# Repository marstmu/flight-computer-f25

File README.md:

# MARS Flight Computer F25

---

<div align="center">
  <div>

    <p><em>3D Render</em></p>
  </div>
  <br>

  <div>
    <br>
    <p><em>Schematic</em></p>
  </div>
  <br>
  
  <div>
    
    <br>
    <em>Footprint</em>
  </div>
</div>

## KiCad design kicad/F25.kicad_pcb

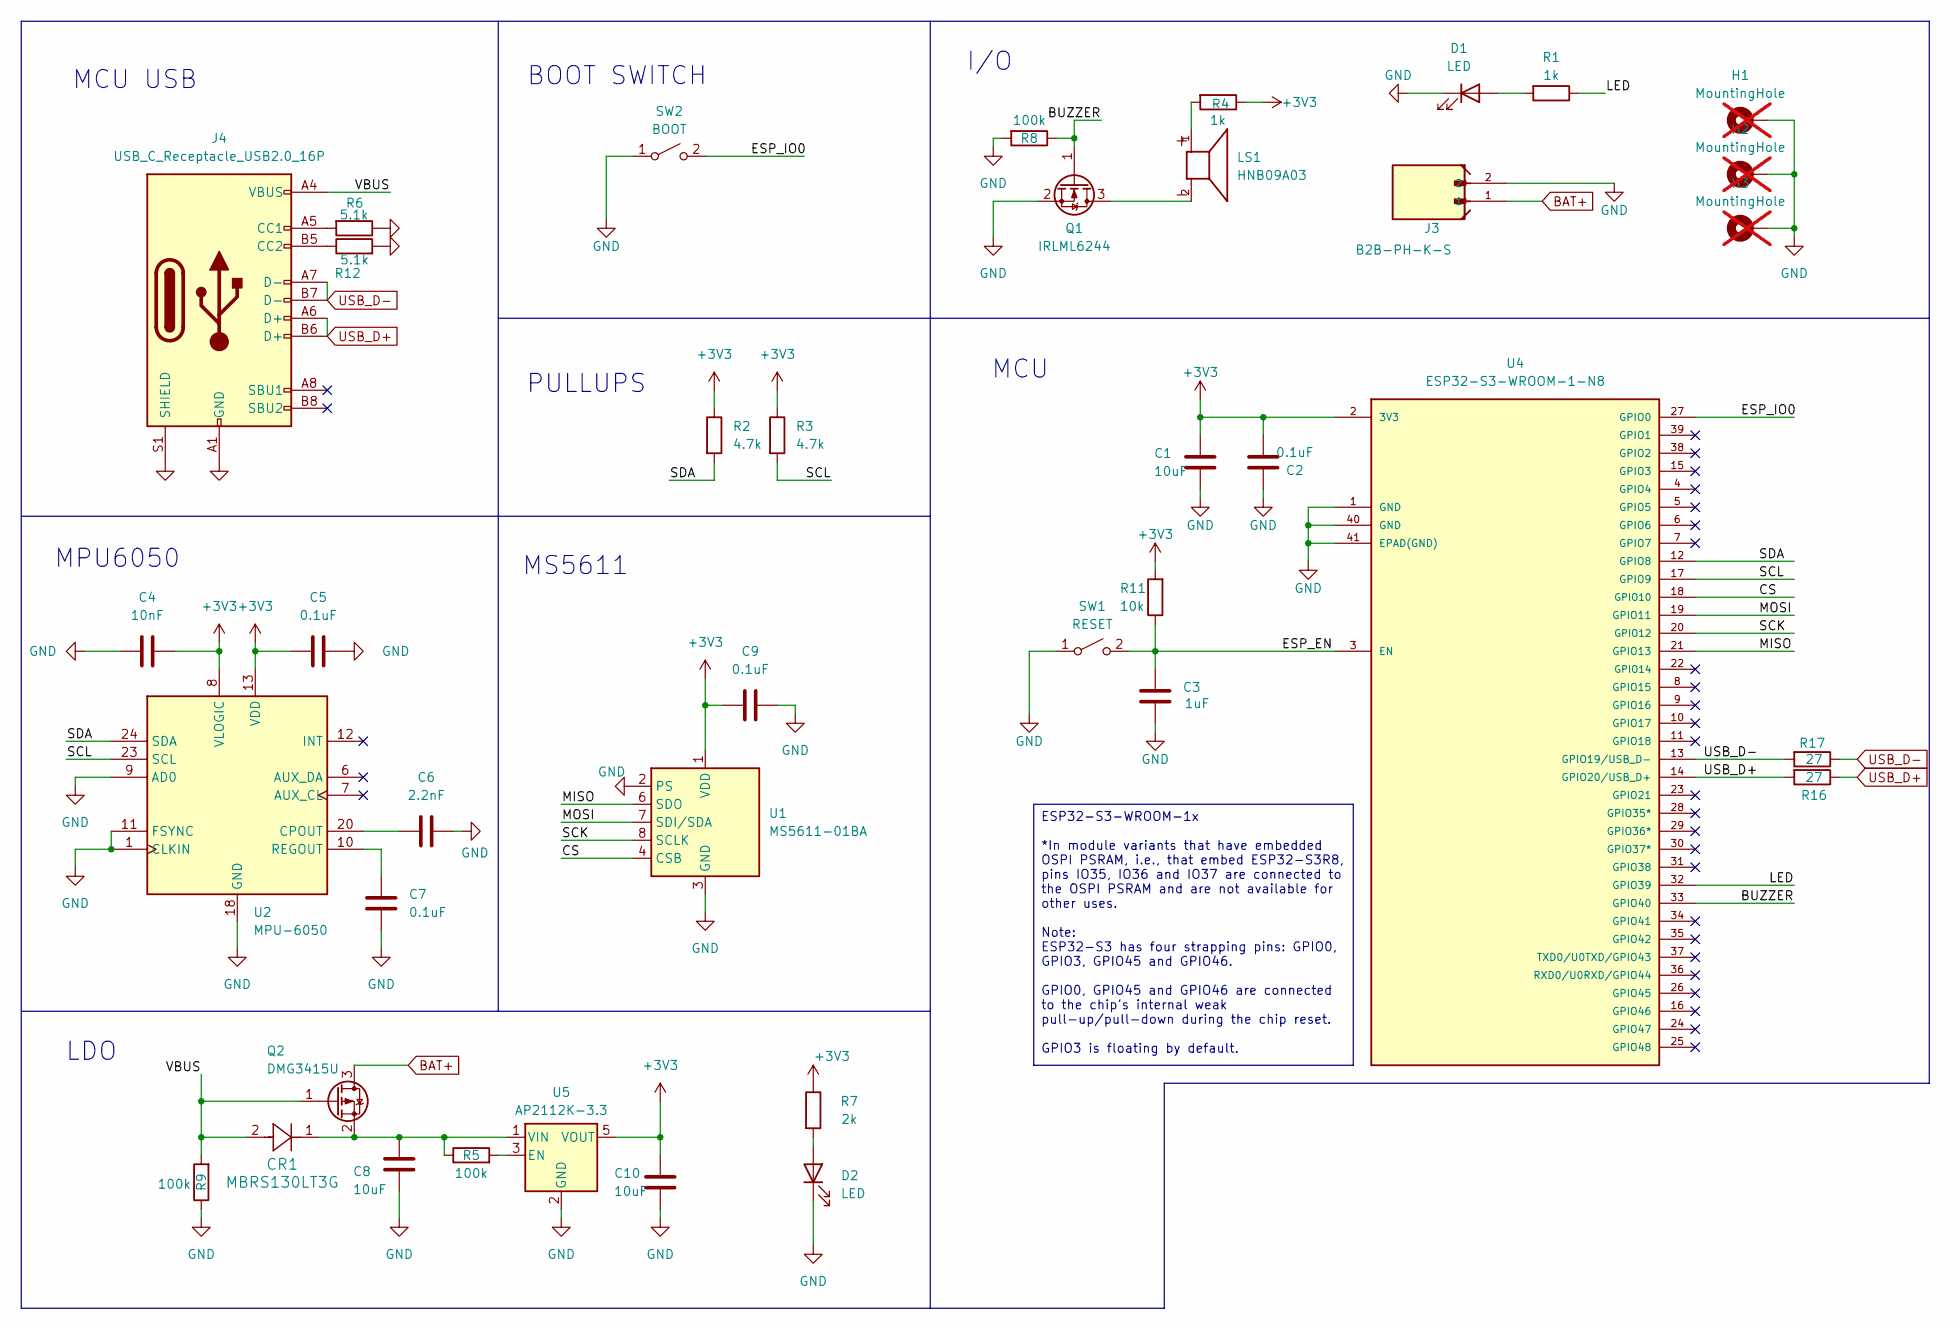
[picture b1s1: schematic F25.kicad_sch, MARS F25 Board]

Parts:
C1, C8, C10: 10uF; C_0402_1005Metric; LCSC C15525
C2, C5, C7, C9: 0.1uF; C_0402_1005Metric; LCSC C1525
C3: 1uF; C_0402_1005Metric; LCSC C52923
C4: 10nF; C_0402_1005Metric; LCSC C15195
C6: 2.2nF; C_0402_1005Metric; LCSC C84703
CR1: MBRS130LT3G; DIODE_SMB_2L_ONS; LCSC C51771
D1: LED; LED_0603_1608Metric; LCSC C2288
D2: LED; LED_0603_1608Metric; LCSC C2290
H1, H2, H3: MountingHole; hole; not fitted
J3: B2B-PH-K-S; JST_B2B-PH-K-S; LCSC C131337
J4: USB_C_Receptacle_USB2.0_16P; USB_C_Receptacle_Palconn_UTC16-G; LCSC Part # C2765186
LS1: HNB09A03; PARTREV C; LCSC C96102
Q1: IRLML6244; SOT-23; LCSC C5123965
Q2: DMG3415U; SOT-23; LCSC C7202986
R1, R4: 1k; C_0402_1005Metric; LCSC C11702
R2, R3: 4.7k; C_0402_1005Metric; LCSC C25900
R5, R8, R9: 100k; C_0402_1005Metric; LCSC C25741
R6, R12: 5.1k; R_0402_1005Metric; LCSC Part # C25905
R7: 2k; C_0402_1005Metric; LCSC C4109
R11: 10k; C_0402_1005Metric; LCSC C25744
R16, R17: 27; R_0402_1005Metric; LCSC Part # C25100
SW1: RESET; SW_SPST_B3U-1000P; LCSC C231329
SW2: BOOT; SW_SPST_B3U-1000P; LCSC C231329
U1: MS5611-01BA; LGA-8_3x5mm_P1.25mm; LCSC C15639
U2: MPU-6050; InvenSense_QFN-24_4x4mm_P0.5mm; LCSC C24112
U4: ESP32-S3-WROOM-1-N8; ESP32-S3-WROOM-1; LCSC C2913198
U5: AP2112K-3.3; SOT_RG1_DIO; LCSC C3021085

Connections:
+3V3: C1.2, C2.2, C4.2, C5.2, C9.1, C10.2, R2.1, R3.1, R4.1, R7.1, R11.2, U1.1 (VDD), U2.8 (VLOGIC), U2.13 (VDD), U4.2 (3V3), U5.5 (VOUT)
/BUZZER: Q1.1 (G), R8.1, U4.33 (GPIO40)
/CS: U1.4 (CSB), U1.5 (CSB), U4.18 (GPIO10)
/ESP_EN: C3.1, R11.1, SW1.2 (B), U4.3 (EN)
/ESP_IO0: SW2.2 (B), U4.27 (GPIO0)
/LED: R1.1, U4.32 (GPIO39)
/MISO: U1.6 (SDO), U4.21 (GPIO13)
/MOSI: U1.7 (SDI/SDA), U4.19 (GPIO11)
/SCK: U1.8 (SCLK), U4.20 (GPIO12)
/SCL: R3.2, U2.23 (SCL), U4.17 (GPIO9)
/SDA: R2.2, U2.24 (SDA), U4.12 (GPIO8)
/VBUS: CR1.2, J4.A4 (VBUS), J4.A9 (VBUS), J4.B4 (VBUS), J4.B9 (VBUS), Q2.1 (G), R9.2
BAT+: J3.1, Q2.3 (D)
GND: C1.1, C2.1, C3.2, C4.1, C5.1, C6.2, C7.2, C8.1, C9.2, C10.1, D1.1 (K), D2.1 (K), H1.1, H2.1, H3.1, J3.2, J4.A1 (GND), J4.A12 (GND), J4.B1 (GND), J4.B12 (GND), J4.S1 (SHIELD), Q1.2 (S), R6.1, R8.2, R9.1, R12.2, SW1.1 (A), SW2.1 (A), U1.2 (PS), U1.3 (GND), U2.1 (CLKIN), U2.9 (AD0), U2.11 (FSYNC), U2.18 (GND), U4.1 (GND), U4.40 (GND), U4.41 (EPAD(GND)), U5.2 (GND)
unnamed: D1.2 (A), R1.2
unnamed: D2.2 (A), R7.2
unnamed: J4.A5 (CC1), R6.2
unnamed: J4.B5 (CC2), R12.1
unnamed: LS1.1, R4.2
unnamed: LS1.2, Q1.3 (D)
unnamed: C8.2, CR1.1, Q2.2 (S), R5.1, U5.1 (VIN)
unnamed: C6.1, U2.20 (CPOUT)
unnamed: C7.1, U2.10 (REGOUT)
unnamed: R5.2, U5.3 (EN)
USB_D+: J4.A6 (D+), J4.B6 (D+), R16.1, R16.2, U4.14 (GPIO20/USB_D+)
USB_D-: J4.A7 (D-), J4.B7 (D-), R17.1, R17.2, U4.13 (GPIO19/USB_D-)

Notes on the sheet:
I/O
MCU
PULLUPS
MPU6050
BOOT SWITCH
MS5611
LDO
MCU USB
ESP32-S3-WROOM-1x *In module variants that have embedded OSPI PSRAM, i.e., that embed ESP32-S3R8, pins IO35, IO36 and IO37 are connected to the OSPI PSRAM and are not available for other uses. Note: ESP32-S3 has four strapping pins: GPIO0, GPIO3, GPIO45 and GPIO46. GPIO0, GPIO45 and GPIO46 are conn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

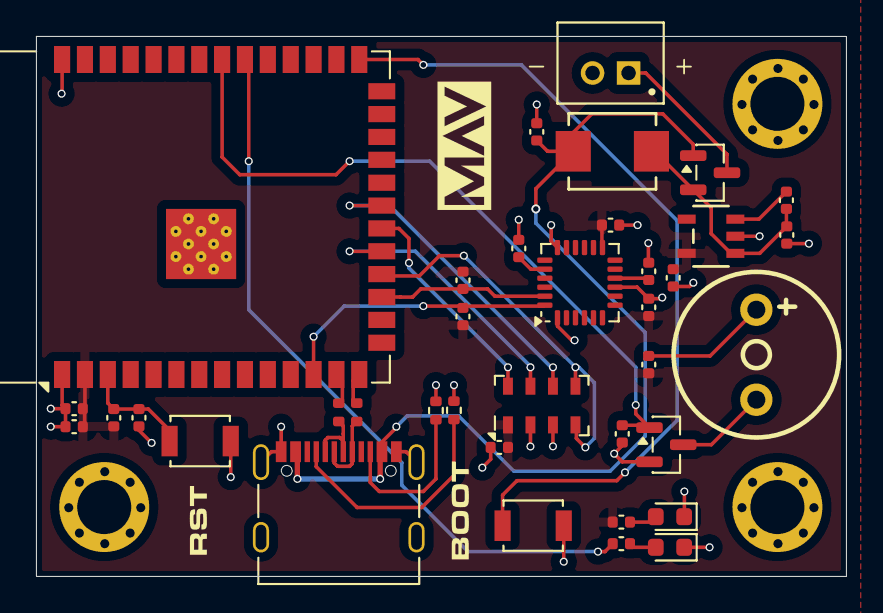
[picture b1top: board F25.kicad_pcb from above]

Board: 2 copper layers, 45.0 x 30.0 mm, 40 parts (0 on the bottom side), 26 nets.

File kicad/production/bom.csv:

Designator,Footprint,Quantity,Value,LCSC Part #
"C1, C10, C8",0402,3,10uF,C15525
"C2, C5, C7, C9",0402,4,0.1uF,C1525
C3,0402,1,1uF,C52923
C4,0402,1,10nF,C15195
C6,0402,1,2.2nF,C84703
CR1,DIODE_SMB_2L_ONS,1,MBRS130LT3G,C51771
D1,0603,1,LED,C2288
D2,0603,1,LED,C2290
J3,JST_B2B-PH-K-S,1,B2B-PH-K-S,C131337
J4,USB_C_Receptacle_Palconn_UTC16-G,1,USB_C_Receptacle_USB2.0_16P,C2765186
LS1,HNB09A03,1,HNB09A03,C96102
Q1,SOT-23,1,IRLML6244,C5123965
Q2,SOT-23,1,DMG3415U,C7202986
"R1, R4",0402,2,1k,C11702
R11,0402,1,10k,C25744
"R12, R6",0402,2,5.1k,C25905
"R16, R17",0402,2,27,C25100
"R2, R3",0402,2,4.7k,C25900
"R5, R8, R9",0402,3,100k,C25741
R7,0402,1,2k,C4109
SW1,SW_SPST_B3U-1000P,1,RESET,C231329
SW2,SW_SPST_B3U-1000P,1,BOOT,C231329
U1,LGA-8_3x5mm_P1.25mm,1,MS5611-01BA,C15639
U2,InvenSense_QFN-24_4x4mm_P0.5mm,1,MPU-6050,C24112
U4,ESP32-S3-WROOM-1,1,ESP32-S3-WROOM-1-N8,C2913198
U5,SOT_RG1_DIO,1,AP2112K-3.3,C3021085

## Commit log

2025-10-02 First Commit
    Added ESP, MPU6050, MS5611, MBRS130L, EEPROM, and LDO
2025-10-02 ESP32-WROOM Connections
    Labelled all pins on module
    Added elementary connections and jumpers
2025-10-02 MPU6050 Connections
    Modified IO22 and IO23 on ESP for I2C lines
    Added capacitors and followed general application note for IMU
2025-10-02 MS6511 Connections
    Added capacitors and connected MS5611 to ESP
2025-10-02 CAT24C512 Connections
    Connected EEPROM module to to ESP
2025-10-02 Buzzer, LDO, and JST connected
    Added connections for LDO, JST, and Buzzer (with NFET) to ESP
2025-10-06 Assigned Footprints
    annotated schematic
    assigned footprints
2025-10-06 Initialized footprint
    Assigned some LCSC part numbers
    Need to update ESP32 footprint to THT
    Need to setup 4 layer board settings
2025-10-06 Lay out almost complete
    aligned parts close to their components
2025-10-06 Finalized board settings
    added ground planes
    added a few 3d parts
    finalized board settings
2025-10-12 Added USB C connections
    Added USB C Receptacle
    Added USB to UART bridge
    Added external circuitry for CP2102N module
2025-10-13 Completed first round of layout
    Did a lot of stuff here ok?
2025-10-14 Updated dates
    Prior to major changes
2025-10-14 Removed Bridge and Flash
    Deleted USB C Connector
    Deleted EEPROM
    Deleted USB to UART Bridge and external circuitry
    Added mounting holes
    Added changes to layout
2025-10-14 Refined Layout
    Removed addditional parts
    Shifted MPU6050 to front
    Shifted Transistor and LDO to front
    Added 3D models for MPU6050 and MBRS diode
2025-10-24 Major Updates
    - Moved all components to front side
    - Added third mounting hole
    - Added most JLC #'s to components
    - Replaced buzzer with one in stock
    - Changed passive components from 1206 to 0402 for assembly
    - Replaced components based on schematic
2025-10-26 Refined Schematic
    - determined TBD values
    - connected MS5611 CSB pin to GND
    - added LEDs to GPIO and power
    - added LCSC numbers for new parts
    - assigned footprints for new parts
2025-10-30 Remove Lock Files
    - Removed Lock files
2025-11-03 Update mounting hole positions
2025-11-03 Add project title to README
2025-11-04 work
2025-11-04 Updates
    work towards S3 module
2025-11-05 Routing Updates to parts
2025-11-07 Update Footprints
2025-11-07 General Updates
2025-11-07 Production Files
2025-11-07 MOVE TO SPI
2025-11-07 Finish SPI MS6511
2025-11-07 Add sponsors
2025-11-11 Font stuff
2025-11-12 Updates to Name
2025-11-12 Update LED Resistors
2025-11-12 LED Updates
2025-11-12 Fix LED Resistors and models
2025-11-12 Update Fabrication
2025-11-12 Add license
2025-11-12 Update copyright holder in LICENSE file
2025-11-13 Add Workflow
2025-11-13 Update Folder Structure
2025-11-13 Update images
2025-11-13 Enhance README with images and descriptions
    Added images and descriptions for the MARS Flight Computer F25.
2025-11-13 Update Silk to SVG
2025-11-13 Add rotate.yml Workflow
2025-11-13 Resize image width in README.md
2025-11-13 MAJOR UPDATES
2025-11-13 MAJOR FIXES
    Fixed Power circuitry
    Added usb power support
    Added pulldown to buzzer (thx taz)
    Removed 10k pullup on gpio3
2025-11-14 Update 3D View
2025-11-14 Update image rotation workflow for GitHub Actions
2025-11-14 Rotate board images
2025-11-14 Update 3D Models
2025-12-11 Add FC Code
2025-12-13 Update main
2025-12-13 📝 Add docstrings to `code`
    Docstrings generation was requested by @anthonydalgliesh.
    * https://github.com/marstmu/flight-computer-f25/pull/5#discussion_r2616128615
    The following files were modified:
    * `MAV_PIO/src/main.cpp`
2025-12-19 fix: Critical errors
2025-12-19 feat: Split code
2025-12-19 feat: Add yaw
2025-12-19 fix: Add yaw argument to snprintf
2025-12-19 feat: Update landing detection
